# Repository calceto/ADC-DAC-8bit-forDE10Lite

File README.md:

# ADC-DAC-8bit-forDE10Lite
 Analog to Digital (and viceversa) convertor as an external stage for the FPGA module DE10Lite by Terasic

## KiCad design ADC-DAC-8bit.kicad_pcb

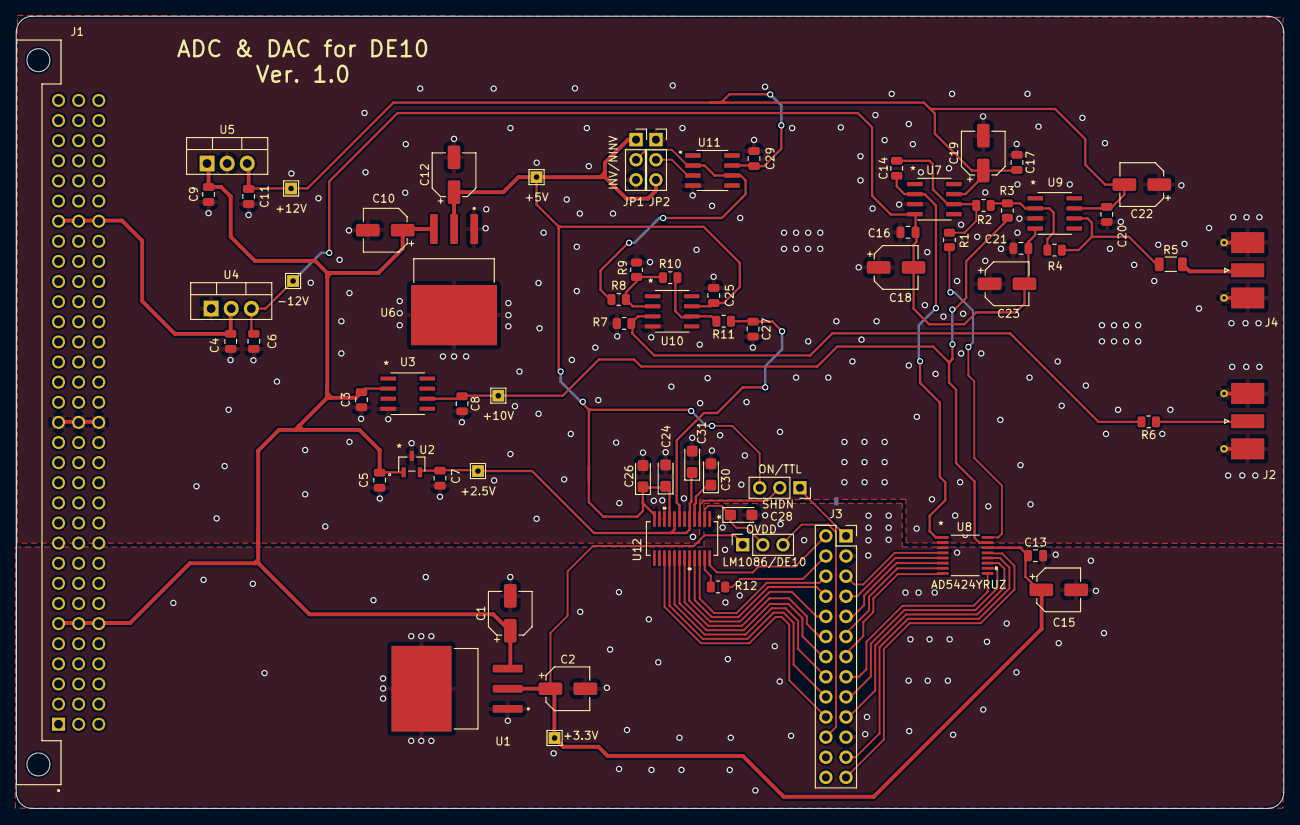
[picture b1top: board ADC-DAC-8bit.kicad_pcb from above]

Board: 2 copper layers, 160.0 x 100.0 mm, 70 parts (1 on the bottom side), 49 nets.

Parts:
+2.5V, +3.3V, +5V, +10V, +12V: TestPoint; TestPoint_THTPad_1.5x1.5mm_Drill0.7mm
-12V: TestPoint; TestPoint_THTPad_1.5x1.5mm_Drill0.7mm
C1, C2, C10, C12, C15, C18, C19, C22, C23: 10u; CP_Elec_5x5.3
C3, C4, C5, C6, C7, C8, C9, C11, C13, C16, C17, C20, C21, C25, C29: 0.1u; C_0805_2012Metric
C14: 4.7p; C_0805_2012Metric
C24, C26, C28, C30, C31: 10u; CP_EIA-3216-10_Kemet-I
C27: 220p; C_0805_2012Metric
J1: 09031967921; 41612-96-C
J2, J4: Conn_Coaxial; SMA_Molex_73251-2120_EdgeMount_Horizontal
J3: Conn_02x13_Odd_Even; PinSocket_2x13_P2.54mm_Vertical
JP1, JP2: Jumper_3_Bridged12; PinSocket_1x03_P2.54mm_Vertical
NT1: NetTie_2; NetTie-2_SMD_Pad0.5mm
OVDD: Jumper_3_Bridged12; PinSocket_1x03_P2.54mm_Vertical
R1, R6: 0R; R_0805_2012Metric
R2: 10k; R_0805_2012Metric
R3, R4: 20k; R_0805_2012Metric
R5: 51R; R_1206_3216Metric
R7, R12: DNF; R_0805_2012Metric
R8: 400R; R_0805_2012Metric
R9: 1k; R_0805_2012Metric
R10: 2k; R_0805_2012Metric
R11: 75R; R_0805_2012Metric
SHDN: Jumper_3_Bridged12; PinSocket_1x03_P2.54mm_Vertical
U1: LM1086IS-3.3; LM1086-IS-5-TO254P1524X483-4N
U2: LT1460KCS3-2.5-TRMPBF
U3: LT1236ACS8-10#PBF; LT1236ACS8-10-PBF
U4: LM7912_TO220; TO-220-3_Vertical
U5: LM7812_TO220; TO-220-3_Vertical
U6: LM1086IS-5.0; LM1086-IS-5-TO254P1524X483-4N
U7, U9: AD8065ARZ
U8: AD5424YRUZ
U10: LT1363; LT1363CS8-TRPBF
U11: OPA1611AIDR; OPA1611-SOIC127P599X175-8N
U12: LTC1406CGN; LTC1406CGN-PBF

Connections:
3.3V-FPGA: J3.22, OVDD.3 (B)
+3.3V: +3.3V.1, C2.1, C13.1, C15.1, OVDD.1 (A), U1.2 (OUT), U8.14 (VDD)
+15VIN: C1.1, C3.1, C5.2, C9.2, C10.1, J1.A6, J1.B6, J1.C6, U1.3 (IN), U2.1 (IN), U3.2 (VIN), U5.1 (VI), U6.3 (IN)
-15VIN: C4.1, J1.A26, J1.B26, J1.C26, U4.2 (VI)
ADC-AIN+: C27.1, R11.1, U12.7 (AIN+)
ADC-AVDD: +5V.1, C12.1, C24.1, C25.2, C26.1, JP1.1 (A), JP2.3 (B), SHDN.3 (B), U6.2 (OUT), U10.7 (V+), U12.9 (AVDD), U12.12 (DVDD)
ADC-CLK: J3.2, U12.24 (CLK)
ADC-D0: J3.20, U12.15 (D0)
ADC-D1: J3.18, U12.16 (D1)
ADC-D2: J3.16, U12.17 (D2)
ADC-D3: J3.14, U12.18 (D3)
ADC-D4: J3.12, U12.19 (D4)
ADC-D5: J3.10, U12.20 (D5)
ADC-D6: J3.8, U12.21 (D6)
ADC-D7: J3.6, U12.22 (D7)
ADC-IN: J2.1 (In), R6.1
ADC-OF/UF: J3.4, R12.1
ADC-OVDD: C28.1, OVDD.2 (C), U12.2 (OVDD)
ADC-SHDN: SHDN.2 (C), U12.3 (~SHDN)
ADC-SHDN-CTRL: J3.1, SHDN.1 (A)
ADC-VBIAS: C30.1, U12.4 (VBIAS)
ADC-VREF: +2.5V.1, C7.2, C31.1, U2.2 (OUT), U12.5 (VREF), U12.8 (AIN-)
DAC-CS: J3.23, U8.12 (~CS)
DAC-D0: J3.19, U8.11 (DB0_(LSB))
DAC-D1: J3.17, U8.10 (DB1)
DAC-D2: J3.15, U8.9 (DB2)
DAC-D3: J3.13, U8.8 (DB3)
DAC-D4: J3.11, U8.7 (DB4)
DAC-D5: J3.9, U8.6 (DB5)
DAC-D6: J3.7, U8.5 (DB6)
DAC-D7: J3.5, U8.4 (DB7)
DAC-OUT: J4.1 (In), R5.2
DAC-RW: J3.25, U8.13 (R/~W)
DAC-V-: C14.1, U7.2 (-IN), U8.1 (IOUT1)
DAC-VREF: +10V.1, C8.1, R3.1, U3.6 (VOUT), U8.15 (VREF)
DAC-VRFB: R1.1, U8.16 (RFB)
GNDA: C3.2, C4.2, C5.1, C6.2, C7.1, C8.2, C9.1, C10.2, C11.1, C12.2, C16.1, C17.1, C18.1, C19.2, C20.1, C21.1, C22.1, C23.1, C24.2, C25.1, C26.2, C27.2, C29.2, C30.2, C31.2, J1.A16, J1.B16, J1.C16, J2.2 (Ext), J4.2 (Ext), JP1.3 (B), JP2.1 (A), NT1.1, R7.2, R9.2, U2.3 (GND), U3.4 (GND), U4.1 (GND), U5.2 (GND), U6.1 (ADJ/GND), U6.4 (GND), U7.3 (+IN), U8.2 (IOUT2), U9.3 (+IN), U10.4 (V-), U11.4 (V-), U12.6 (AGND), U12.10 (AGND), U12.11 (DGND)
GNDD: C1.2, C2.2, C13.2, C15.2, C28.2, J3.3, J3.21, NT1.2, U1.1 (ADJ/GND), U1.4 (GND), U8.3 (GND), U12.1 (OGND)
unnamed: C14.2, R1.2, R2.1, U7.6 (VOUT)
unnamed: JP2.2 (C), U11.3 (+IN)
unnamed: R2.2, R3.2, R4.1, U9.2 (-IN)
unnamed: R4.2, R5.1, U9.6 (VOUT)
unnamed: R6.2, R7.1, U10.3 (+)
unnamed: R10.1, R11.2, U10.6
unnamed: R8.1, R9.1, R10.2, U10.2 (-)
unnamed: R12.2, U12.23 (OF/UF)
OPAMP-REF: JP1.2 (C), R8.2, U11.2 (-IN), U11.6 (OUT)
VS+: +12V.1, C11.2, C17.2, C19.1, C20.2, C22.2, C29.1, U5.3 (VO), U7.7 (+VS), U9.7 (+VS), U11.7 (V+)
VS-: -12V.1, C6.1, C16.2, C18.2, C21.2, C23.2, U4.3 (VO), U7.4 (-VS), U9.4 (-VS)

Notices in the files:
parts and their libraries:
Copyright 2021 Accelerated Designs. All rights reserved.
